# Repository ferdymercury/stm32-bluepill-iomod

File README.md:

# STM32-BluePill Digital I/O Board

This Open Source Hardware PCB proyect is a tool for teach µController (microcontroller) programming. Feel free to use, modifie or improobe it in any way you want. The schematics and the layout was designed on [KiCad EDA Software](https://kicad.org/).

More information (Spanish only): [Modulo I/O Digital para BluePill STM32F1](https://electronlinux.wordpress.com/2020/06/11/modulo-i-o-digital-para-bluepill-stm32f1-en-kicad/)

- - -

Este PCB es un poryecto de Hardware Libre y Abierto, pensado para enseñar programación de µControladores (microcontroladores). Sientase libre de usarlo, modificarlo y/o mejorarlo en cualquier sentido que desee. Los esquemáticos y el PCB fueron diseñados utilizando el software [KiCad EDA](https://kicad.org/).

- - -

# Pinout Configuration

## OUTPUTS

| PIN  | Conection     | Active | | PIN  | Conection     | Active |
|------|---------------|--------|-|------|---------------|--------|
| PB9  | LED1 - Red    | LOW    | | PA0  |  Seg E        |  HIGH  |
| PB8  | LED1 - Green  | LOW    | | PA1  |  Seg D        |  HIGH  |
| PB7  | LED1 - Blue   | LOW    | | PA2  |  Seg P        |  HIGH  | 
| PB6  | LED2          | LOW    | | PA3  |  Seg C        |  HIGH  |
| PB5  | LED3          | LOW    | | PA4  |  Seg G        |  HIGH  |
| PB4  | LED4          | LOW    | | PA5  |  Seg B        |  HIGH  |
| PA11 | LED5          | LOW    | | PA6  |  Seg F        |  HIGH  |
| PC13 | Build-in LED  | LOW    | | PA7  |  Seg A        |  HIGH  |
|  -   |      -        |   -    | | PB0  |  Disp 1 (MSD) |  LOW   |
|  -   |      -        |   -    | | PB1  |  Disp 2       |  LOW   |
|  -   |      -        |   -    | | PB10 |  Disp 3       |  LOW   |
|  -   |      -        |   -    | | PB11 |  Disp 4 (LSD) |  LOW   |

## INPUTS

| PIN  | Conection     | Active |
|------|---------------|--------|
| PB13 | Rotary - A    | LOW    |
| PA15 | Rotary - B    | LOW    |
| PA12 | Rotary Switch | LOW    |
| PB15 | Button 1      | LOW    |
| PB14 | Button 2      | LOW    |
| PA13 | Button 3      | LOW    |
| PA12 | Button 4      | LOW    |

## Reference

## Images

|  | |
|-|-|
|<p style="text-align:center;">top layout</p>|<p style="text-align:center;">bottom layout</p>|

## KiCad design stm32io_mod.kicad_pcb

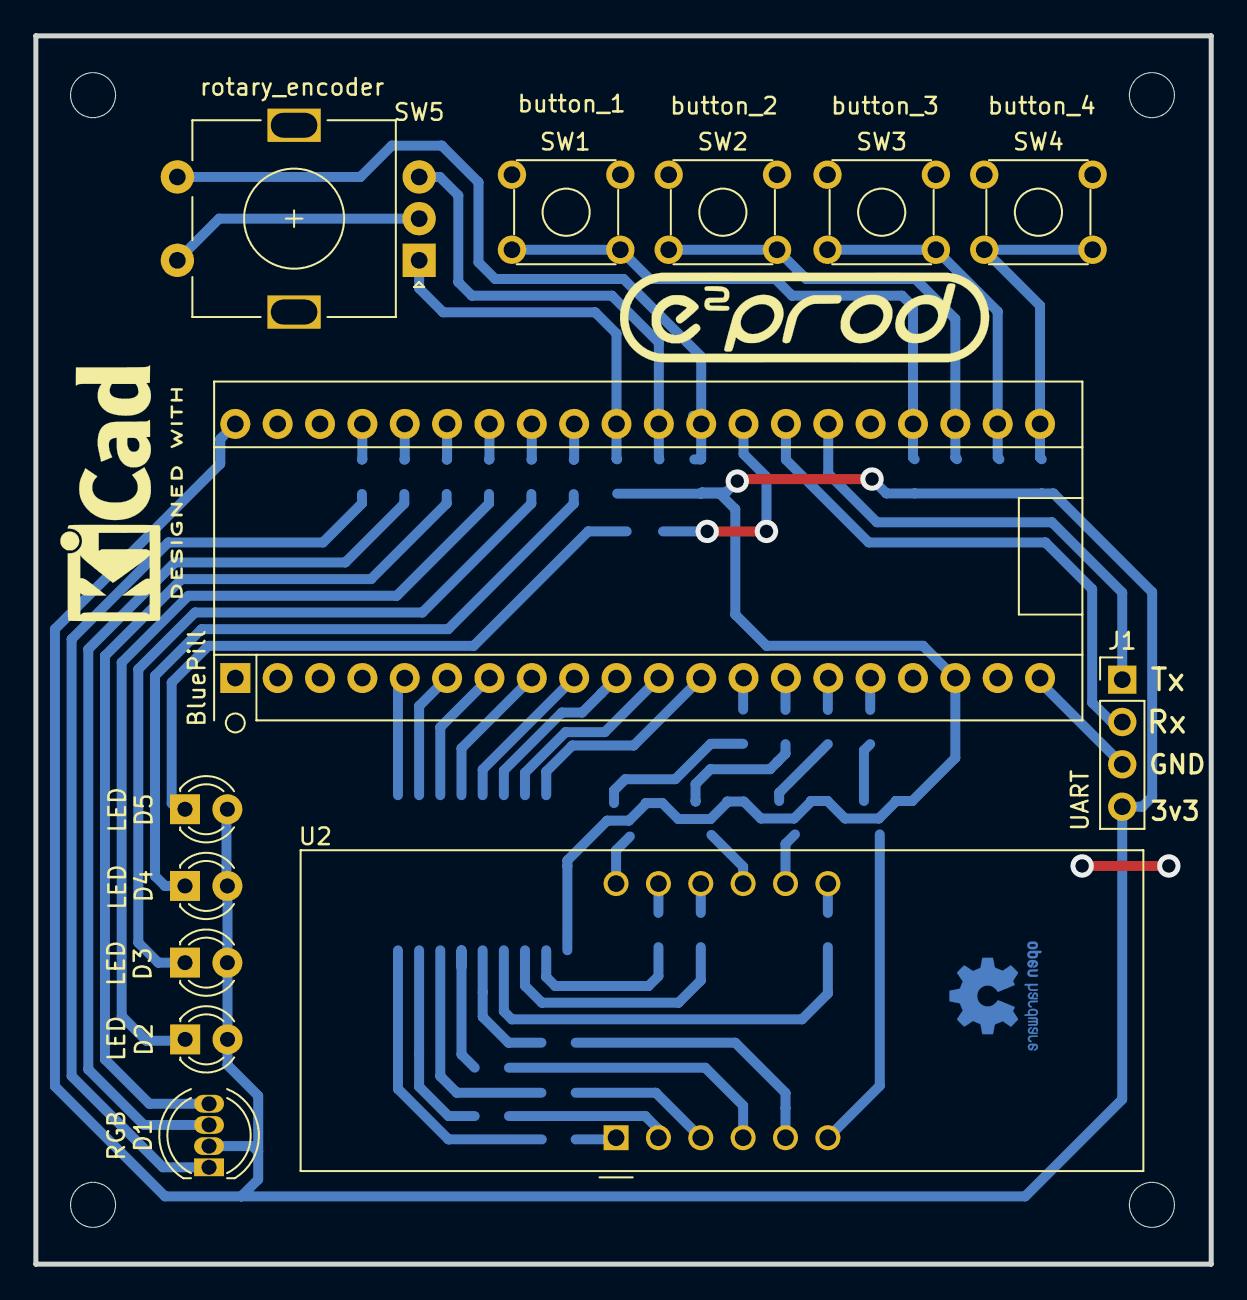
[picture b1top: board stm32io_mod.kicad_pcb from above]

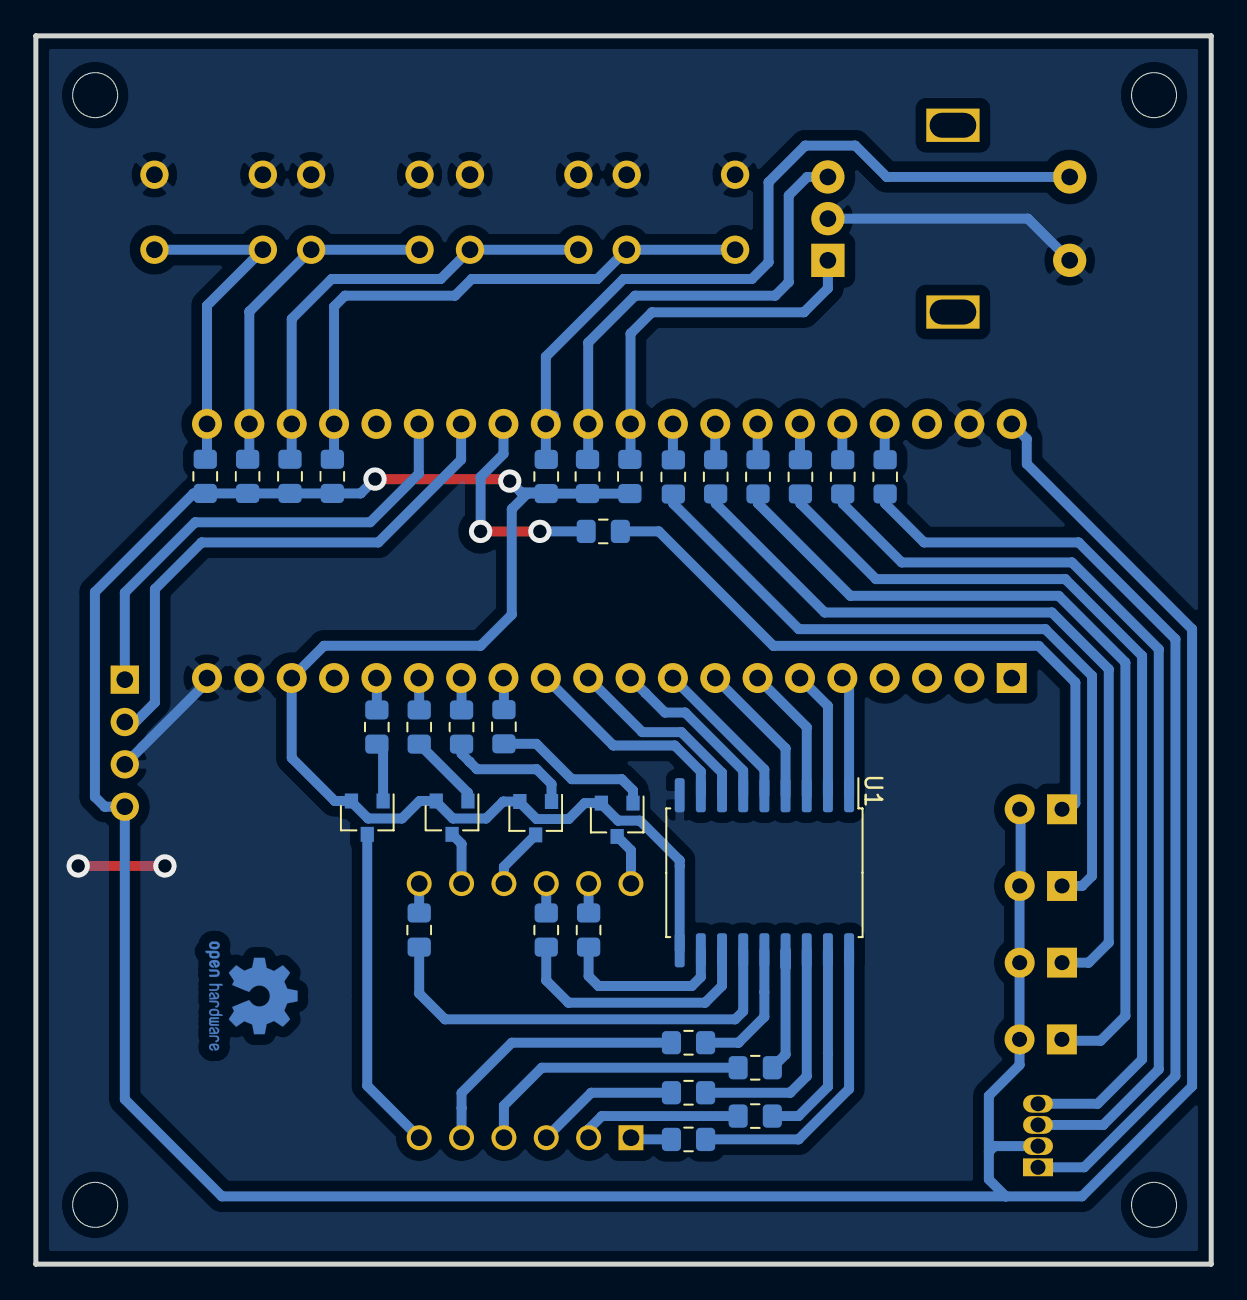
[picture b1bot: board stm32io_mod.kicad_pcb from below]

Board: 2 copper layers, 70.5 x 73.7 mm, 44 parts (31 on the bottom side), 61 nets.

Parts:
D1: RGB; LED_D5.0mm-4_RGB
D2, D3, D4, D5: LED; LED_D3.0mm_Clear
J1: UART; PinHeader_1x04_P2.54mm_Vertical
M1: BluePill
Q1, Q2, Q3, Q4: BC858; SOT-23
R1, R2, R11, R12, R13, R14, R16: 10k; R_0805_2012Metric_Pad1.15x1.40mm_HandSolder
R3, R4, R5, R6, R7, R8, R9, R10: 47Ω; R_0805_2012Metric_Pad1.15x1.40mm_HandSolder
R17, R18, R19, R22, R23, R24, R25: 100Ω; R_0805_2012Metric_Pad1.15x1.40mm_HandSolder
R20, R21, R26, R27: 2k7; R_0805_2012Metric_Pad1.15x1.40mm_HandSolder
SW1: button_1; SW_TH_Tactile_Omron_B3F-10xx
SW2: button_2; SW_TH_Tactile_Omron_B3F-10xx
SW3: button_3; SW_TH_Tactile_Omron_B3F-10xx
SW4: button_4; SW_TH_Tactile_Omron_B3F-10xx
SW5: rotary_encoder; RotaryEncoder_Alps_EC11E-Switch_Vertical_H20mm
U1: ULN2803A; SOIC-18W_7.5x11.6mm_P1.27mm
U2: CA56-12SRWA

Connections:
GND: J1.3, M1.19, M1.20, M1.39, SW1.3, SW1.4, SW2.3, SW2.4, SW3.3, SW3.4, SW4.3, SW4.4, SW5.C, SW5.S2, U1.9
unnamed: D1.1, R17.1
unnamed: D1.3, R18.1
unnamed: D1.4, R19.1
unnamed: D2.1, R22.1
unnamed: D3.1, R23.1
unnamed: D4.1, R24.1
unnamed: D5.1, R25.1
unnamed: M1.5, U1.1
unnamed: M1.6, U1.2
unnamed: M1.7, U1.3
unnamed: M1.8, U1.4
unnamed: M1.9, U1.5
unnamed: M1.10, U1.6
unnamed: M1.11, U1.7
unnamed: M1.12, U1.8
unnamed: Q1.1, R21.2
unnamed: Q1.3, U2.12
unnamed: Q2.1, R27.2
unnamed: Q2.3, U2.9
unnamed: Q3.1, R20.2
unnamed: Q3.3, U2.8
unnamed: Q4.1, R26.2
unnamed: Q4.3, U2.6
unnamed: R3.1, U1.14
unnamed: R4.1, U1.12
unnamed: R5.1, U1.11
unnamed: R6.1, U1.13
unnamed: R7.1, U1.18
unnamed: R8.1, U1.17
unnamed: R9.1, U1.15
unnamed: R10.1, U1.16
Rx: J1.2, M1.27
Tx: J1.1, M1.26
VCC: D1.2, D2.2, D3.2, D4.2, D5.2, J1.4, M1.18, M1.40, Q1.2, Q2.2, Q3.2, Q4.2, R1.2, R2.2, R11.2, R12.2, R13.2, R14.1, R16.1, U1.10
led1: M1.34, R22.2
led2: M1.33, R23.2
led3: M1.32, R24.2
led4: M1.28, R25.2
ledb: M1.35, R19.2
ledg: M1.36, R18.2
ledr: M1.37, R17.2
rotA: M1.31, R13.1, SW5.A
rotB: M1.30, R14.2, SW5.B
seg1: M1.13, R21.1
seg2: M1.14, R27.1
seg3: M1.15, R20.1
seg4: M1.16, R26.1
segA: R5.2, U2.11
segB: R6.2, U2.7
segC: R9.2, U2.4
segD: R8.2, U2.2
segE: R7.2, U2.1
segF: R4.2, U2.10
segG: R3.2, U2.5
segP: R10.2, U2.3
sw1: M1.24, R1.1, SW1.1, SW1.2
sw2: M1.23, R11.1, SW2.1, SW2.2
sw3: M1.22, R2.1, SW3.1, SW3.2
sw4: M1.21, R12.1, SW4.1, SW4.2
swr: M1.29, R16.2, SW5.S1

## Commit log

2021-01-25 Mejorando alguna rutas el PCB
2021-11-10 Update README.md
    https://forum.kicad.info/t/warning-avoid-all-links-to-kicad-pcb-org-use-kicad-org/31521

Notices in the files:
stm32io_mod.kicad_pcb:
MIT License
Copyright (c) 2020 Matías S. Ávalos (msavalos@gmail.com)
